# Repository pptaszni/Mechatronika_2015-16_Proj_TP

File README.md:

# Mechatronika_2015-16_Proj_TP
Mechatronika w pojazdach samochodowych - projekt.

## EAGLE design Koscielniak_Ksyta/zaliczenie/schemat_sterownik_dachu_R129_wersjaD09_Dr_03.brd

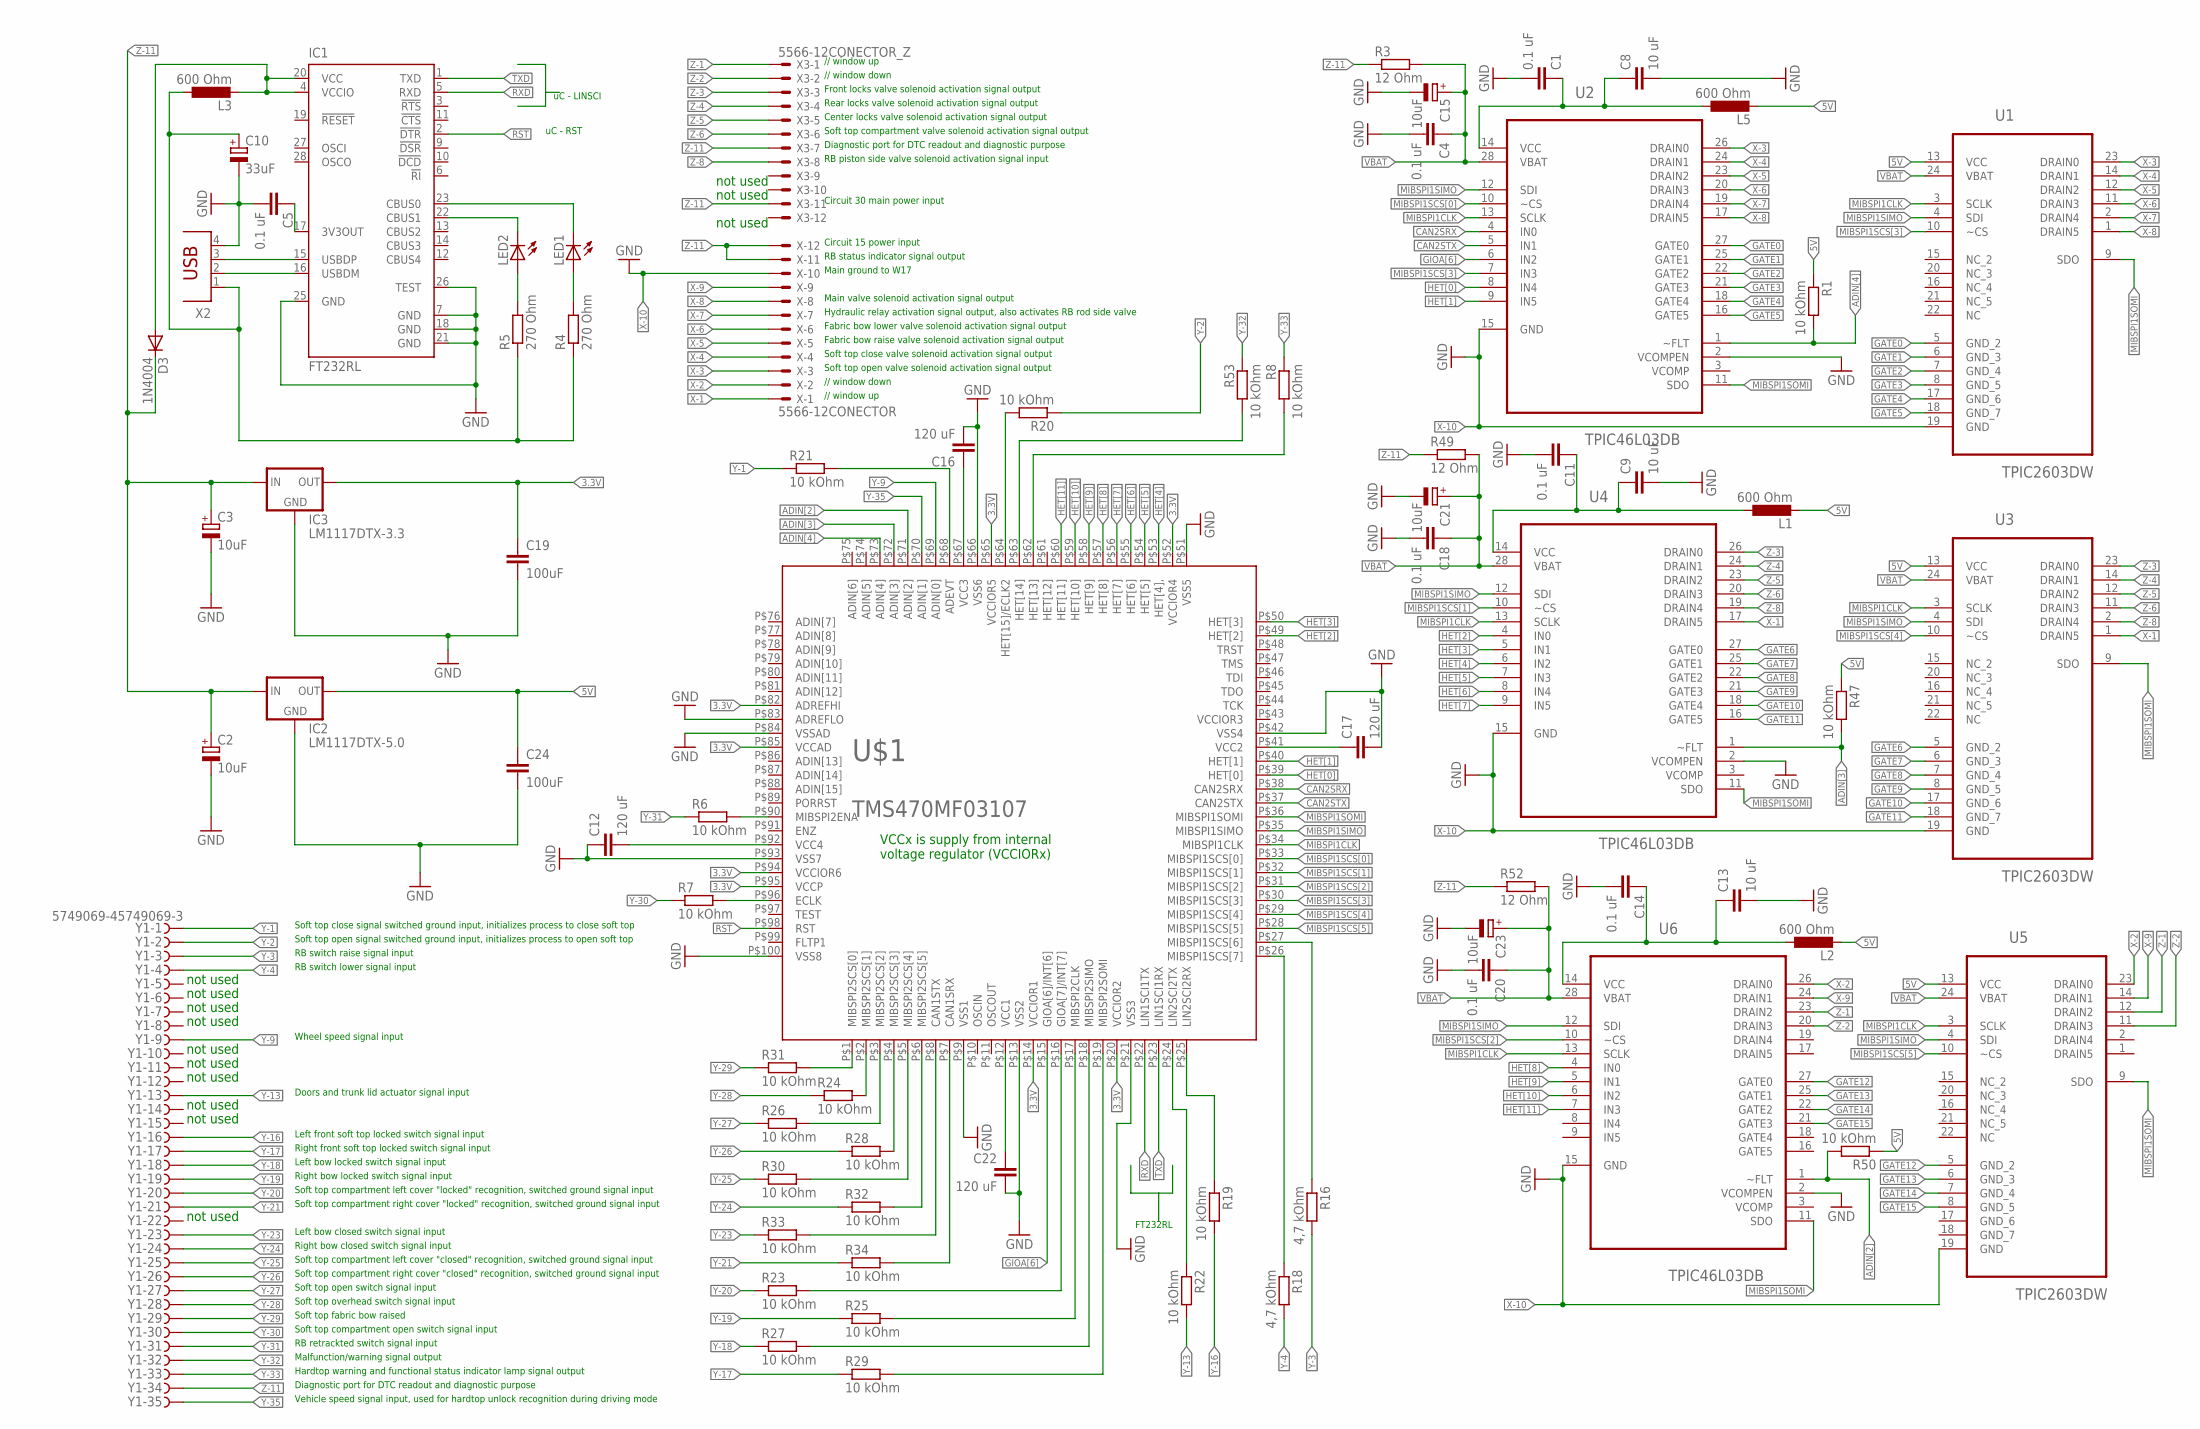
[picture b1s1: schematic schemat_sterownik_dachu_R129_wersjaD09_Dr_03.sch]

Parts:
C1, C4, C5, C11, C14, C18, C20: 0.1 uF; C0805
C2, C3, C15, C21, C23: 10uF; SMC_C
C8, C9, C13: 10 uF; C0805
C10: 33uF; SMC_C
C12, C16, C17, C22: 120 uF; C3225
C19, C24: 100uF; C1210
D3: 1N4004; DO41-10
IC1: FT232RL; SSOP28
IC2: LM1117DTX-5.0; TO252
IC3: LM1117DTX-3.3; TO252
L1, L2, L3, L5: 600 Ohm; L3216C
LED1, LED2: LEDCHIPLED_1206; CHIPLED_1206
R1, R6, R7, R8, R19, R20, R21, R22, R23, R24, R25, R26, R27, R28, R29, R30, R31, R32, R33, R34, R47, R50, R53: 10 kOhm; R0603
R3, R49, R52: 12 Ohm; R0603
R4, R5: 270 Ohm; R0603
R16, R18: 4,7 kOhm; R0603
U1, U3, U5: TPIC2603DW; SOIC127P1030X265-24N
U2, U4, U6: TPIC46L03DB; SOP65P780X200-28N
U$1: TMS470MF03107; S-PQFP-G100
X: 5566-12CONECTOR; 5566-12
X2: PN61729
X3: 5566-12CONECTOR_Z; 5566-12
Y1: 5749069-45749069-3; 5749069-4

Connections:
3.3V: C19.1, IC3.TAB (OUT), U$1.P$14 (VCCIOR1), U$1.P$20 (VCCIOR2), U$1.P$52 (VCCIOR4), U$1.P$65 (VCCIOR5), U$1.P$82 (ADREFHI), U$1.P$85 (VCCAD), U$1.P$94 (VCCIOR6), U$1.P$95 (VCCP)
5V: C24.1, D3.A, IC1.4 (VCCIO), IC1.20 (VCC), IC2.TAB (OUT), L1.2, L2.2, L3.2, L5.2, R1.1, R47.1, R50.1, U1.13 (VCC), U3.13 (VCC), U5.13 (VCC)
ADIN[2]: R50.2, U6.1 (~FLT), U$1.P$71 (ADIN[2])
ADIN[3]: R47.2, U4.1 (~FLT), U$1.P$72 (ADIN[3])
ADIN[4]: R1.2, U2.1 (~FLT), U$1.P$73 (ADIN[4])
CAN2SRX: U2.4 (IN0), U$1.P$38 (CAN2SRX)
CAN2STX: U2.5 (IN1), U$1.P$37 (CAN2STX)
GATE0: U1.5 (GND_2), U2.27 (GATE0)
GATE1: U1.6 (GND_3), U2.25 (GATE1)
GATE2: U1.7 (GND_4), U2.22 (GATE2)
GATE3: U1.8 (GND_5), U2.21 (GATE3)
GATE4: U1.17 (GND_6), U2.18 (GATE4)
GATE5: U1.18 (GND_7), U2.16 (GATE5)
GATE6: U3.5 (GND_2), U4.27 (GATE0)
GATE7: U3.6 (GND_3), U4.25 (GATE1)
GATE8: U3.7 (GND_4), U4.22 (GATE2)
GATE9: U3.8 (GND_5), U4.21 (GATE3)
GATE10: U3.17 (GND_6), U4.18 (GATE4)
GATE11: U3.18 (GND_7), U4.16 (GATE5)
GATE12: U5.5 (GND_2), U6.27 (GATE0)
GATE13: U5.6 (GND_3), U6.25 (GATE1)
GATE14: U5.7 (GND_4), U6.22 (GATE2)
GATE15: U5.8 (GND_5), U6.21 (GATE3)
GIOA[6]: U2.6 (IN2), U$1.P$15 (GIOA[6]/INT[6])
GND: C1.2, C2.-, C3.-, C4.2, C5.2, C8.2, C9.2, C10.-, C11.2, C12.1, C13.2, C14.2, C15.-, C16.2, C17.2, C18.2, C19.2, C20.2, C21.-, C22.2, C23.-, C24.2, IC1.7 (GND), IC1.18 (GND), IC1.21 (GND), IC1.25 (GND), IC1.26 (TEST), IC2.1 (GND), IC3.1 (GND), U2.2 (VCOMPEN), U4.2 (VCOMPEN), U6.2 (VCOMPEN), U$1.P$9 (VSS1), U$1.P$13 (VSS2), U$1.P$21 (VSS3), U$1.P$42 (VSS4), U$1.P$51 (VSS5), U$1.P$66 (VSS6), U$1.P$83 (ADREFLO), U$1.P$84 (VSSAD), U$1.P$93 (VSS7), U$1.P$100 (VSS8), X2.4
HET[0]: U2.8 (IN4), U$1.P$39 (HET[0])
HET[1]: U2.9 (IN5), U$1.P$40 (HET[1])
HET[2]: U4.4 (IN0), U$1.P$49 (HET[2])
HET[3]: U4.5 (IN1), U$1.P$50 (HET[3])
HET[4]: U4.6 (IN2), U$1.P$53 (HET[4],)
HET[5]: U4.7 (IN3), U$1.P$54 (HET[5])
HET[6]: U4.8 (IN4), U$1.P$55 (HET[6])
HET[7]: U4.9 (IN5), U$1.P$56 (HET[7])
HET[8]: U6.4 (IN0), U$1.P$57 (HET[8])
HET[9]: U6.5 (IN1), U$1.P$58 (HET[9])
HET[10]: U6.6 (IN2), U$1.P$59 (HET[10])
HET[11]: U6.7 (IN3), U$1.P$60 (HET[11])
HET[13]: R8.2, U$1.P$62 (HET[13])
HET[14]: R53.2, U$1.P$63 (HET[14])
MIBSPI1CLK: U1.3 (SCLK), U2.13 (SCLK), U3.3 (SCLK), U4.13 (SCLK), U5.3 (SCLK), U6.13 (SCLK), U$1.P$34 (MIBSPI1CLK)
MIBSPI1SCS[0]: U2.10 (~CS), U$1.P$33 (MIBSPI1SCS[0])
MIBSPI1SCS[1]: U4.10 (~CS), U$1.P$32 (MIBSPI1SCS[1])
MIBSPI1SCS[2]: U6.10 (~CS), U$1.P$31 (MIBSPI1SCS[2])
MIBSPI1SCS[3]: U1.10 (~CS), U2.7 (IN3), U$1.P$30 (MIBSPI1SCS[3])
MIBSPI1SCS[4]: U3.10 (~CS), U$1.P$29 (MIBSPI1SCS[4])
MIBSPI1SCS[5]: U5.10 (~CS), U$1.P$28 (MIBSPI1SCS[5])
MIBSPI1SIMO: U1.4 (SDI), U2.12 (SDI), U3.4 (SDI), U4.12 (SDI), U5.4 (SDI), U6.12 (SDI), U$1.P$35 (MIBSPI1SIMO)
MIBSPI1SOMI: U1.9 (SDO), U2.11 (SDO), U3.9 (SDO), U4.11 (SDO), U5.9 (SDO), U6.11 (SDO), U$1.P$36 (MIBSPI1SOMI)
unnamed: R7.2, U$1.P$96 (ECLK)
unnamed: C16.1, U$1.P$67 (VCC3)
unnamed: C17.1, U$1.P$41 (VCC2)
unnamed: R6.2, U$1.P$90 (MIBSPI2ENA)
unnamed: R26.2, U$1.P$3 (MIBSPI2SCS[2])
unnamed: R20.2, U$1.P$64 (HET[15]/ECLK2)
unnamed: R21.2, U$1.P$68 (ADEVT)
unnamed: R18.1, U$1.P$26 (MIBSPI1SCS[7])
unnamed: C5.1, IC1.17 (3V3OUT)
unnamed: IC1.22 (CBUS1), LED2.C
unnamed: C22.1, U$1.P$12 (VCC1)
unnamed: C12.2, U$1.P$92 (VCC4)
unnamed: IC1.16 (USBDM), X2.2
unnamed: IC1.15 (USBDP), X2.3
unnamed: IC1.23 (CBUS0), LED1.C
unnamed: C1.1, C8.1, L5.1, U2.14 (VCC)
unnamed: LED1.A, R4.2
unnamed: LED2.A, R5.2
unnamed: R16.1, U$1.P$27 (MIBSPI1SCS[6])
unnamed: R23.2, U$1.P$16 (GIOA[7]/INT[7])
unnamed: R25.2, U$1.P$17 (MIBSPI2CLK)
unnamed: R27.2, U$1.P$18 (MIBSPI2SIMO)
unnamed: R29.2, U$1.P$19 (MIBSPI2SOMI)
unnamed: R22.1, U$1.P$24 (LIN2SCI2TX)
unnamed: R19.1, U$1.P$25 (LIN2SCI2RX)
unnamed: R34.2, U$1.P$7 (CAN1SRX)
unnamed: R33.2, U$1.P$8 (CAN1STX)
unnamed: R32.2, U$1.P$6 (MIBSPI2SCS[5])
unnamed: R30.2, U$1.P$5 (MIBSPI2SCS[4])
unnamed: R28.2, U$1.P$4 (MIBSPI2SCS[3])
unnamed: R24.2, U$1.P$2 (MIBSPI2SCS[1])
unnamed: R31.2, U$1.P$1 (MIBSPI2SCS[0])
unnamed: C9.1, C11.1, L1.1, U4.14 (VCC)
unnamed: C13.1, C14.1, L2.1, U6.14 (VCC)
RST: IC1.2 (!DTR), U$1.P$98 (RST)
RXD: IC1.5 (RXD), U$1.P$22 (LIN1SCI1TX)
TXD: IC1.1 (TXD), U$1.P$23 (LIN1SCI1RX)
VBAT: C4.1, C15.+, C18.1, C20.1, C21.+, C23.+, R3.2, R49.2, R52.2, U1.24 (VBAT), U2.28 (VBAT), U3.24 (VBAT), U4.28 (VBAT), U5.24 (VBAT), U6.28 (VBAT)
VCC: C10.+, L3.1, R4.1, R5.1, X2.1
X-1: U3.1 (DRAIN5), U4.17 (DRAIN5), X.1
X-2: U5.23 (DRAIN0), U6.26 (DRAIN0), X.2
X-3: U1.23 (DRAIN0), U2.26 (DRAIN0), X.3
X-4: U1.14 (DRAIN1), U2.24 (DRAIN1), X.4
X-5: U1.12 (DRAIN2), U2.23 (DRAIN2), X.5
X-6: U1.11 (DRAIN3), U2.20 (DRAIN3), X.6
X-7: U1.2 (DRAIN4), U2.19 (DRAIN4), X.7
X-8: U1.1 (DRAIN5), U2.17 (DRAIN5), X.8
X-9: U5.14 (DRAIN1), U6.24 (DRAIN1), X.9
X-10: U1.19 (GND), U2.15 (GND), U3.19 (GND), U4.15 (GND), U5.19 (GND), U6.15 (GND), X.10
Y-1: R21.1, Y1.1
Y-2: R20.1, Y1.2
Y-3: R16.2, Y1.3
Y-4: R18.2, Y1.4
Y-9: U$1.P$69 (ADIN[0]), Y1.9
Y-13: R22.2, Y1.13
Y-16: R19.2, Y1.16
Y-17: R29.1, Y1.17
Y-18: R27.1, Y1.18
Y-19: R25.1, Y1.19
Y-20: R23.1, Y1.20
Y-21: R34.1, Y1.21
Y-23: R33.1, Y1.23
Y-24: R32.1, Y1.24
Y-25: R30.1, Y1.25
Y-26: R28.1, Y1.26
Y-27: R26.1, Y1.27
Y-28: R24.1, Y1.28
Y-29: R31.1, Y1.29
Y-30: R7.1, Y1.30
Y-31: R6.1, Y1.31
Y-32: R53.1, Y1.32
Y-33: R8.1, Y1.33
Y-35: U$1.P$70 (ADIN[1]), Y1.35
Z-1: U5.12 (DRAIN2), U6.23 (DRAIN2), X3.1
Z-2: U5.11 (DRAIN3), U6.20 (DRAIN3), X3.2
Z-3: U3.23 (DRAIN0), U4.26 (DRAIN0), X3.3
Z-4: U3.14 (DRAIN1), U4.24 (DRAIN1), X3.4
Z-5: U3.12 (DRAIN2), U4.23 (DRAIN2), X3.5
Z-6: U3.11 (DRAIN3), U4.20 (DRAIN3), X3.6
Z-8: U3.2 (DRAIN4), U4.19 (DRAIN4), X3.8
Z-11: C2.+, C3.+, D3.C, IC2.2 (IN), IC3.2 (IN), R3.1, R49.1, R52.1, X.11, X.12, X3.7, X3.11, Y1.34

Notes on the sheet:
not used
FT232RL
uC - LINSCI
uC - RST
VCCx is supply from internal voltage regulator (VCCIORx)
Soft top open valve solenoid activation signal output
Soft top close valve solenoid activation signal output
Fabric bow raise valve solenoid activation signal output
Fabric bow lower valve solenoid activation signal output
Hydraulic relay activation signal output, also activates RB rod side valve
Main valve solenoid activation signal output
Main ground to W17
RB status indicator signal output
Circuit 15 power input
Front locks valve solenoid activation signal output
Rear locks valve solenoid activation signal output
Center locks valve solenoid activation signal output
Soft top compartment valve solenoid activation signal output
Diagnostic port for DTC readout and diagnostic purpose
RB piston side valve solenoid activation signal input
Circuit 30 main power input
Soft top close signal switched ground input, initializes process to close soft top
Soft top open signal switched ground input, initializes process to open soft top
RB switch raise signal input
RB switch lower signal input
Wheel speed signal input
Doors and trunk lid actuator signal input
Left front soft top locked switch signal input
Right front soft top locked switch signal input
Left bow locked switch signal input
Right bow locked switch signal input
Soft top compartment left cover "locked" recognition, switched ground signal input
Soft top compartment right cover "locked" recognition, switched ground signal input
Left bow closed switch signal input
Right bow closed switch signal input
Soft top compartment left cover "closed" recognition, switched ground signal input
Soft top compartment right cover "closed" recognition, switched ground signal input
Soft top open switch signal input
Soft top overhead switch signal input
Soft top fabric bow raised

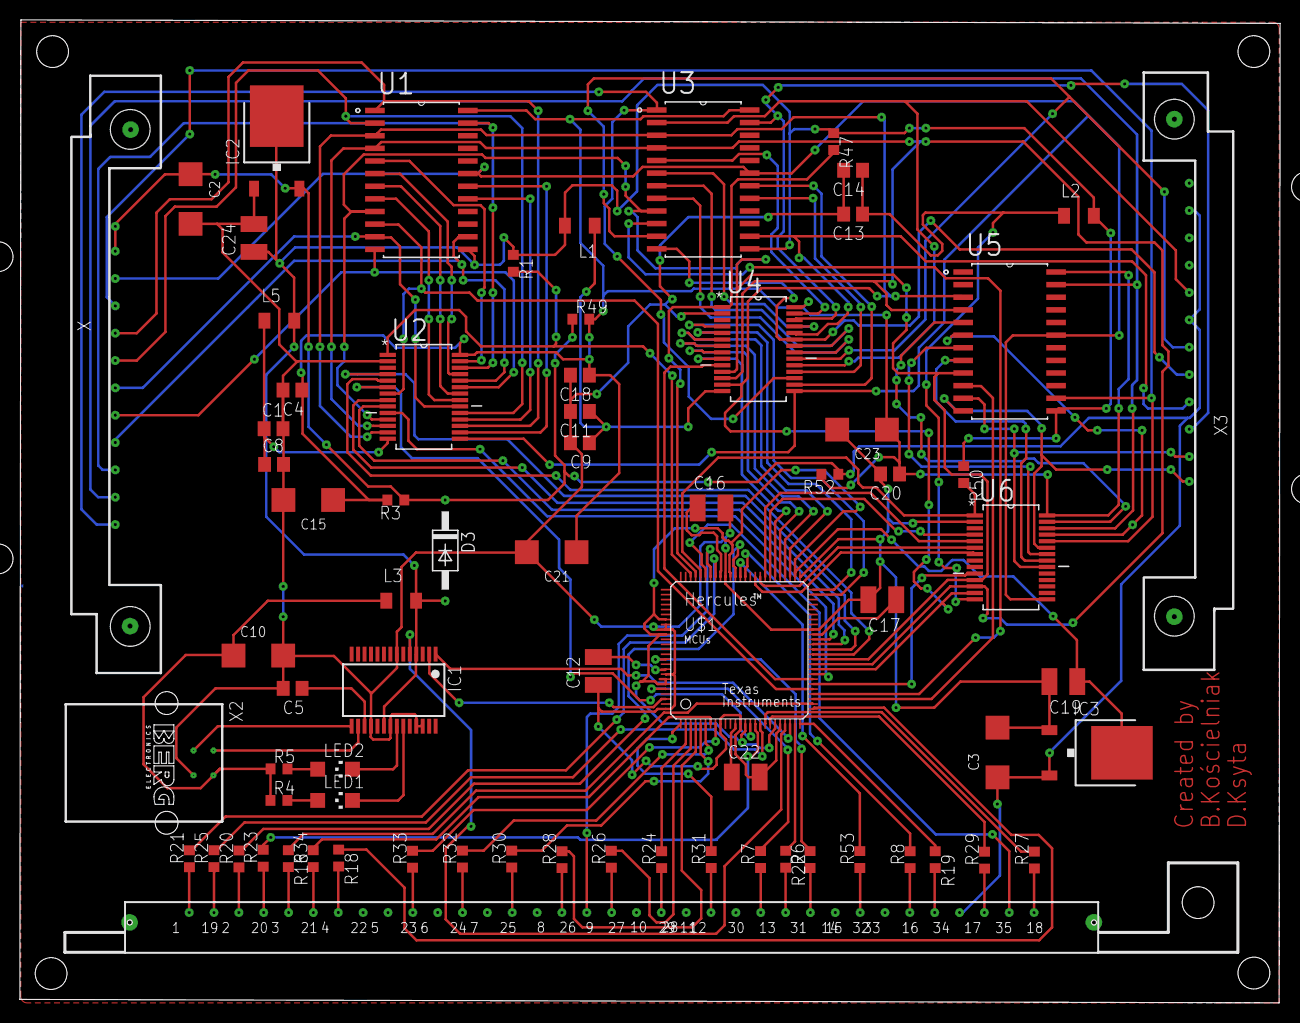
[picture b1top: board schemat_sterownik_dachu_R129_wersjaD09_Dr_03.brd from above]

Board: 2 copper layers, 126.8 x 98.9 mm, 73 parts (0 on the bottom side), 129 nets.

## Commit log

2016-03-02 Dodana instrukcja do pierwszego zadania i tematy projektow z Nokii, moze kogos zainteresuja.
2016-03-02 Zmodyfikowane daty w instrukcji
2016-03-07 Test
2016-03-07 Create Drelich
2016-03-07 Update Drelich
2016-03-08 Added files via upload
2016-03-08 dodanie pliku
2016-03-08 COMMIT_EDITMSG
2016-03-08 Dodane i modyfikowane pliki -zalozenia_projektowe.txt -jakas_nazwa.txt
2016-03-09 Create zalozenia_projektowe
2016-03-09 Create przyklad
2016-03-09 Create Sklad
2016-03-09 Create Zalozenia projektowe
2016-03-09 Create Komponenty
2016-03-09 Create Bartsch
2016-03-10 wprowadzono plik
2016-03-10 Dodalam plik Dorota do folderu Kardas
2016-03-12 Create Ksyta
2016-03-15 Zostaly dodane zalozenia projektowe.
2016-03-15 Dodany sklad grupy
2016-03-16 dodanie folderu
2016-03-16 usuniecie folderu
2016-03-16 Dodalem komentarz do zalozen projektowych
2016-03-16 Added files via upload
    Co tu dużo gadać, algorytm z podziałem na wątki.
2016-03-16 Dodalem sklad grupy
2016-03-16 Dodalem zalozenia projektowe
2016-03-16 usuwam plik
2016-03-16 Dodalem folder
2016-03-17 Revert "Założenia projektowe"
2016-03-17 Usunięcie założeń projektowych (zmiana projektu)
2016-03-17 Temat projektu
2016-03-18 Tworze folder projektu
2016-03-18 Dodaje podzial zadan
2016-03-18 Dodaje wykres Gantta do projektu
2016-03-19 Update Zalozenia projektowe
2016-03-22 dodanie zalozen
    ith '#' will be ignored, and an empty message aborts the commit.
    On branch mater
2016-03-23 Dodana nowa koncepcja projektu
2016-03-29 Update zalozenia_projektowe
    dodaliśmy komentarz odnośnie efektów pracy przy projekcie
2016-03-30 Dodalem warunki zaliczenia - system oceniania. Kazdy z punktow mozemy przedyskutowac/zmienic, jezeli zaistnieje taka potrzeba
2016-03-30 Dokumentacja wersja na stan dzisiejszy
    Ogólnie specyfikacja wejść/wyjść układu oraz opis poszczególnych sekwencji realizowanych podczas procesu.
2016-03-30 Skrót dokumentacji elementów elektronicznych
    Tak jak w nazwie. Zawiera informacje skrótowe o tym, co posiadają elementy elektroniczne znajdujące się na oryginalnym sterowniku. Pełne dokumentacje techniczne posiadamy na dyskach.
2016-03-30 Pełny schemat elektryczny wejść/wyjść sterownika
    Zawiera również opis zespołów podłączonych do układu oraz poszczególnych wejść/wyjść pinów na sterowniku.
2016-04-01 Aktualny raport z postępu prac
2016-04-02 Aktualna wersja apki
2016-04-05 Dodano informacje odnosnie postepow prac oraz noty katalogowe.
2016-04-06 Dodany komentarz odnonie zasiêgu czujnika
2016-04-14 nowa koncepcja sterownika + dokumentacje
    Raport z przebiegu prac w pliku koncepcja.pdf
2016-04-23 Dodano opis uk³adu elektronicznego
2016-04-28 Schemat elektroniczny
    Użyte elementy:
    -Arduino UNO,
    -2 silniki DC,
    -mostek H: L293D,
    -4 akumulatory AAA,
    -przetwornica S7V7F5 (na schemacie LM2931, ponieważ nie ma S7V7F5 w bibliotece programu),
2016-05-07 Added files via upload
    Program systemu gaśniczego
    Film przedstawiający działanie programu: https://www.youtube.com/watch?v=7YZ2LtWuBc0&feature=youtu.be
    Poprzednia wersja programu omyłkowo nie została przez nas wgrana.
2016-05-16 Wersja aplikacji po teście połączenia z ELM327
2016-05-22 Schemat elektryczny - wersja ostateczna
    Wspomniana wcześniej w komentarzach wersja ostateczna schematu elektrycznego. Dopiero teraz, bo były jeszcze malutkie zmiany, przy zamawianiu części. Jesteśmy na etapie rzeźbienia płytki. Trochę spra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
2016-05-24 Dodano schemat elektryczny
2016-05-24 Szybka aktualizacja postępów
2016-05-25 Screen z testu aplikacji
2016-05-29 Poprawiliśmy schemat
    Detekcję obrazu robimy czysto programowo. Mamy nagrany obraz i pracujemy nad algorytmem, tylko tak jak wcześniej wspomniałem mało czasu jest.
2016-06-02 Projekt płytki
    Tak ma wyglądać nasza płytka po żmudnej pracy łączenia ścieżek. Nie było to takie proste jak myśleliśmy, bo nie mogliśmy zbytnio skorzystać z funkcji auto-routingu ze względu na to, że w układzie wed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
2016-06-03 Link do arkusza z waszymi ocenami
2016-06-03 Add files via upload
    Oto wykonany finalnie projekt, kod + działający program. Tutaj link do filmu z poprzedniej wersji (z działającym wyświetlaczem, diodą i buzzerem - https://www.youtube.com/watch?v=7YZ2LtWuBc0 )
2016-06-03 Add files via upload
    Elementy elektroniczne i mechaniczne czekające na zmontowanie. Na zdjęciach brak drugiego silniczka (jest już w podwoziu) i rezystorów (zapomniałem umieścić).
2016-06-03 Add files via upload
    Nazwa pliku była identyczna z już istniejącą w folderze, może dlatego nie przeszło. To całość
2016-06-03 Add files via upload
    Nazwa była identyczna z już obecną, dlatego program nie przeszedł. Wspólnie podjęliśmy decyzję, że chcielibyśmy ocenę na podstawie filmu. Byłoby to nam bardzo na rękę z powodu zaliczeń.
2016-06-04 Prawie finalna wersja aplikacji z dodanymi obrotomierzami
2016-06-04 Film i screen obrotomierzy
    Wrzucam film z dzisiejszego testu, jak widać aplikacja działa sprawnie, regularnie sczytuje parametry. Jedynie jest problem, bo w przypadku niektórych parametrów, które ostatnio działały, były błędy 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
2016-06-08 Ocena projektu
2016-06-10 Create pliki zaliczeniowe
2016-06-12 Add files via upload
    Wiem, że już po deadline, ale dosyłam kolejny etap mojego projektu.
    Niestety, samochodzik nie jeździ, ponieważ mam problem z zasilaniem. USB+arduino mają za mało mocy i próba ruszenia silniczkiem powoduje restart mikrokontrolera. Próbuję też użyć zewnętrznego zasilan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
    Obecnie w testach kodu zamiast włączania silników włączam diody.
2016-06-12 Wstawiamy ostateczna wersje algorytmu automatycznych swiatel drogowych. W celu dokladniejszego zrozumienia dzialania przeczytaj plik omowienie.txt.
2016-06-13 Końcowa wersja aplikacji
2016-06-13 Film i screeny z działania i raport końcowy
2016-06-14 Wystawiam ocene i dodaje pliki, z ktorymi mieliscie problem
2016-06-15 Wystawiam ocene za projekt
2016-06-15 Przyznam, ze mam problem ze stworzeniem pliku makefile dla opencv, bo kompilator wywala mi, ze nie moze znalezc lokalizacji opencv\cv.h i reszty plikow pewnie tez. Jezeli chodzi o integracje obu czes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
2016-06-15 Przyznam, ze mam problem ze stworzeniem pliku makefile dla opencv, bo kompilator wywala mi, ze nie moze znalezc lokalizacji opencv\cv.h i reszty plikow pewnie tez.
    Jezeli chodzi o integracje obu czesci to nie bardzo rozumiemy co ma Pan na mysli? Bo szczerze mowiac wydaje nam sie ze nic takiego nie zakladalismy. Byla czesc czysto programowa, ktora miala analizow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
2016-06-18 Oddamy ostateczna wersje do konca poniedzialku
2016-06-20 Ostateczne odanie projektu Prosze sie najpierw zapoznac z plikiem "Raport koncowy.pdf" tam jest wszystko opisane.
2016-06-24 dodalem schemat
2016-06-24 dodalem plytke
